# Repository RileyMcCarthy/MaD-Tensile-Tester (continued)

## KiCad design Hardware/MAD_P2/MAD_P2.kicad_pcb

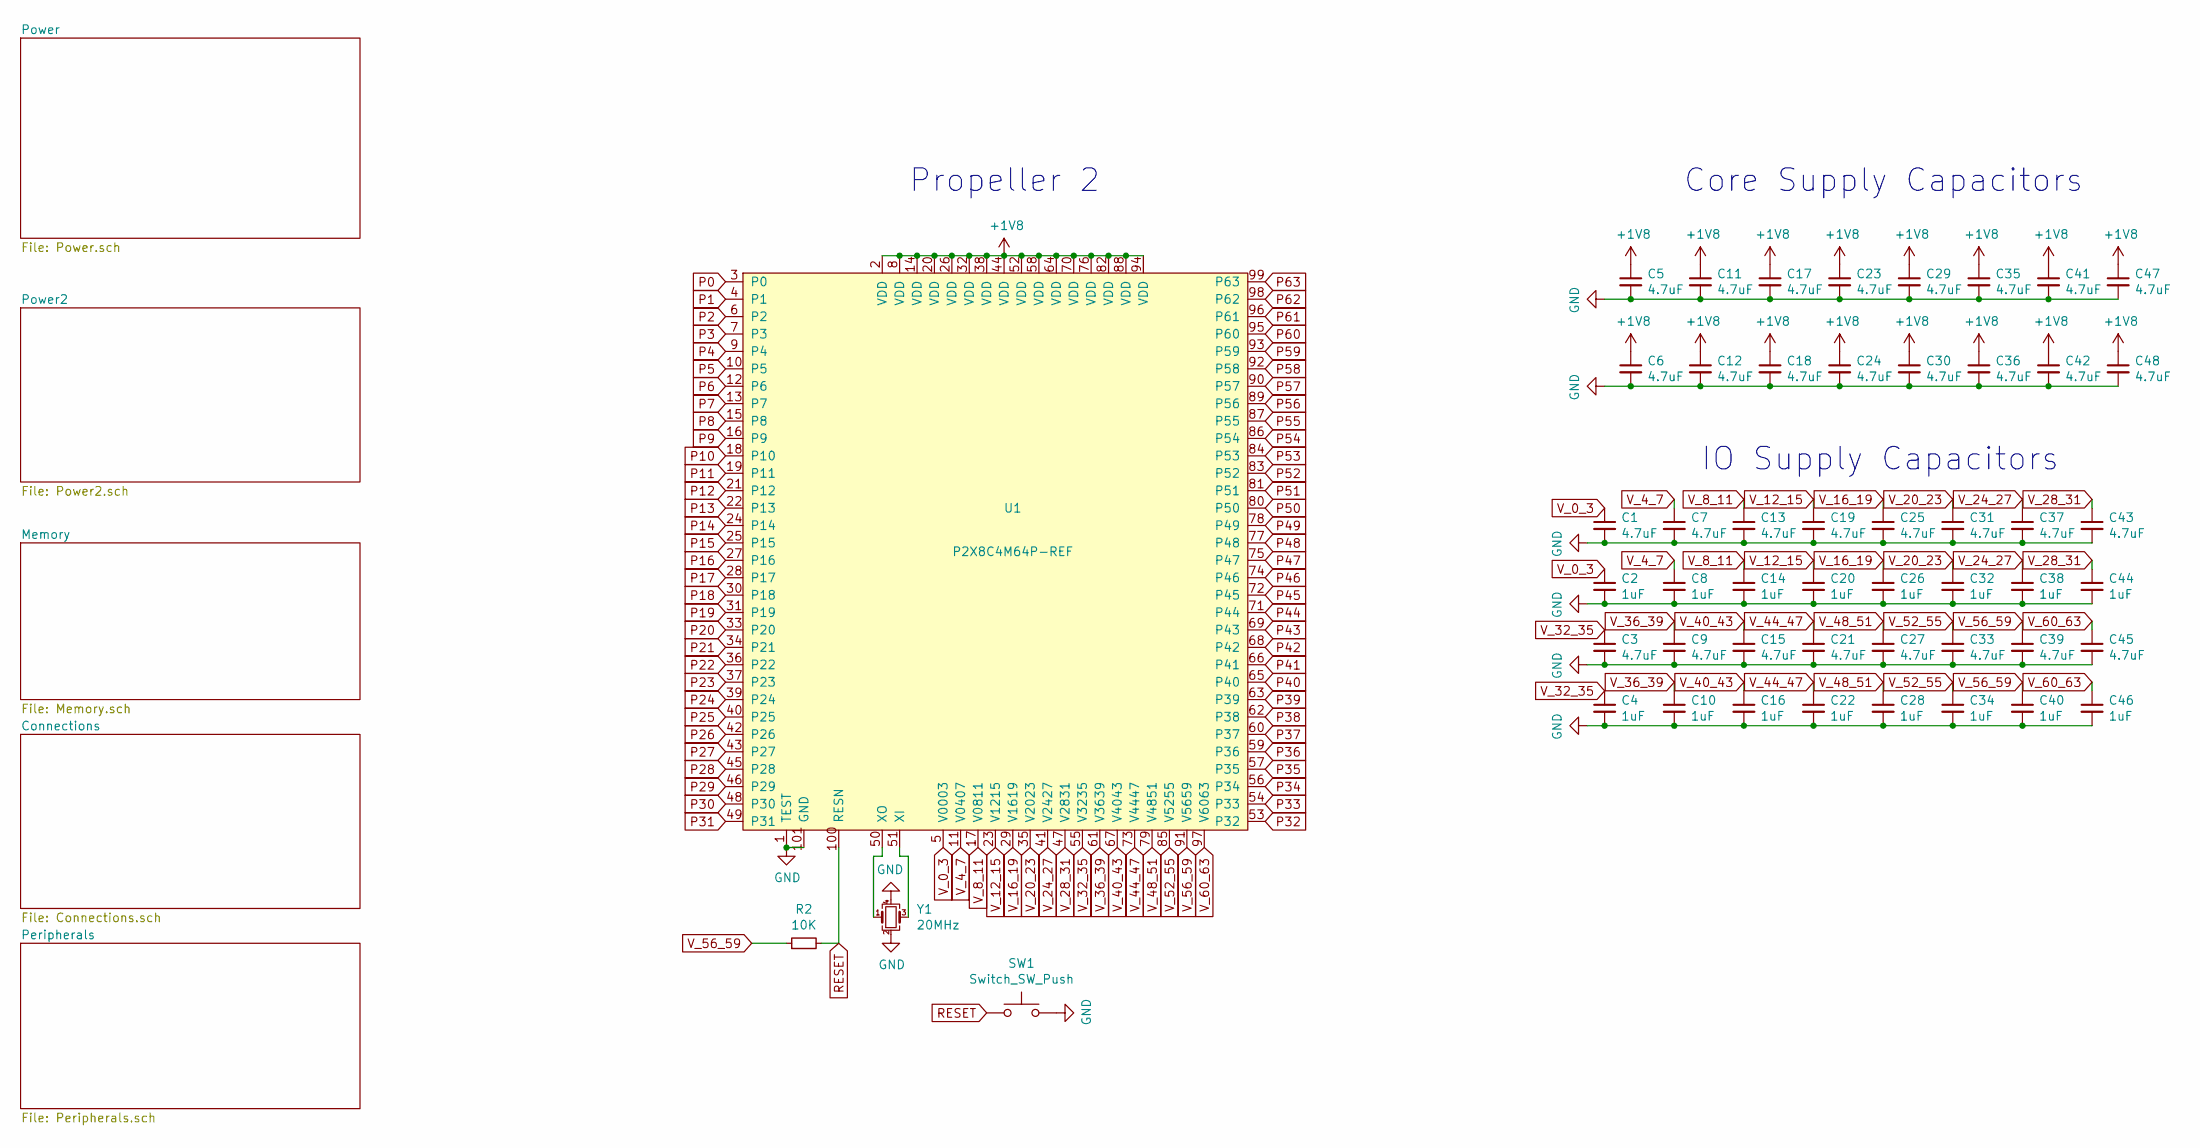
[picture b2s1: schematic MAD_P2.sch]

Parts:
C1, C3, C5, C6, C7, C9, C11, C12, C13, C15, C17, C18, C19, C21, C23, C24, C25, C27, C29, C30, C31, C33, C35, C36, C37, C39, C41, C42, C43, C45, C47, C48: 4.7uF; C_0603_1608Metric; LCSC C19666
C2, C4, C8, C10, C14, C16, C20, C22, C26, C28, C32, C34, C38, C40, C44, C46: 1uF; C_0603_1608Metric; LCSC C15849
R2: 10K; R_0603_1608Metric; LCSC C25804
SW1: Switch_SW_Push; SW_PUSH_6mm
U1: P2X8C4M64P-REF; TQFP-100-1EP_14x14mm_P0.5mm_EP5x5mm_ThermalVias; DIGIKEY 149-P2X8C4M64P-ND
Y1: 20MHz; Crystal_SMD_3225-4Pin_3.2x2.5mm; LCSC C110936

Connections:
+1V8: C5.1, C6.1, C11.1, C12.1, C17.1, C18.1, C23.1, C24.1, C29.1, C30.1, C35.1, C36.1, C41.1, C42.1, C47.1, C48.1, U1.2 (VDD), U1.8 (VDD), U1.14 (VDD), U1.20 (VDD), U1.26 (VDD), U1.32 (VDD), U1.38 (VDD), U1.44 (VDD), U1.52 (VDD), U1.58 (VDD), U1.64 (VDD), U1.70 (VDD), U1.76 (VDD), U1.82 (VDD), U1.88 (VDD), U1.94 (VDD); also elsewhere on the board
GND: C1.2, C2.2, C3.2, C4.2, C5.2, C6.2, C7.2, C8.2, C9.2, C10.2, C11.2, C12.2, C13.2, C14.2, C15.2, C16.2, C17.2, C18.2, C19.2, C20.2, C21.2, C22.2, C23.2, C24.2, C25.2, C26.2, C27.2, C28.2, C29.2, C30.2, C31.2, C32.2, C33.2, C34.2, C35.2, C36.2, C37.2, C38.2, C39.2, C40.2, C41.2, C42.2, C43.2, C44.2, C45.2, C46.2, C47.2, C48.2, SW1.2, U1.1 (TEST), U1.101 (GND), Y1.2, Y1.4; also elsewhere on the board
unnamed: U1.50 (XO), Y1.1
unnamed: U1.51 (XI), Y1.3
P0: U1.3 (P0); also elsewhere on the board
P1: U1.4 (P1); also elsewhere on the board
P2: U1.6 (P2); also elsewhere on the board
P3: U1.7 (P3); also elsewhere on the board
P4: U1.9 (P4); also elsewhere on the board
P5: U1.10 (P5); also elsewhere on the board
P6: U1.12 (P6); also elsewhere on the board
P7: U1.13 (P7); also elsewhere on the board
P8: U1.15 (P8); also elsewhere on the board
P9: U1.16 (P9); also elsewhere on the board
P10: U1.18 (P10); also elsewhere on the board
P11: U1.19 (P11); also elsewhere on the board
P12: U1.21 (P12); also elsewhere on the board
P13: U1.22 (P13); also elsewhere on the board
P14: U1.24 (P14); also elsewhere on the board
P15: U1.25 (P15); also elsewhere on the board
P16: U1.27 (P16); also elsewhere on the board
P17: U1.28 (P17); also elsewhere on the board
P18: U1.30 (P18); also elsewhere on the board
P19: U1.31 (P19); also elsewhere on the board
P20: U1.33 (P20); also elsewhere on the board
P21: U1.34 (P21); also elsewhere on the board
P22: U1.36 (P22); also elsewhere on the board
P23: U1.37 (P23); also elsewhere on the board
P24: U1.39 (P24); also elsewhere on the board
P25: U1.40 (P25); also elsewhere on the board
P26: U1.42 (P26); also elsewhere on the board
P27: U1.43 (P27); also elsewhere on the board
P28: U1.45 (P28); also elsewhere on the board
P29: U1.46 (P29); also elsewhere on the board
P30: U1.48 (P30); also elsewhere on the board
P31: U1.49 (P31); also elsewhere on the board
P32: U1.53 (P32); also elsewhere on the board
P33: U1.54 (P33); also elsewhere on the board
P34: U1.56 (P34); also elsewhere on the board
P35: U1.57 (P35); also elsewhere on the board
P36: U1.59 (P36); also elsewhere on the board
P37: U1.60 (P37); also elsewhere on the board
P38: U1.62 (P38); also elsewhere on the board
P39: U1.63 (P39); also elsewhere on the board
P40: U1.65 (P40); also elsewhere on the board
P41: U1.66 (P41); also elsewhere on the board
P42: U1.68 (P42); also elsewhere on the board
P43: U1.69 (P43); also elsewhere on the board
P44: U1.71 (P44); also elsewhere on the board
P45: U1.72 (P45); also elsewhere on the board
P46: U1.74 (P46); also elsewhere on the board
P47: U1.75 (P47); also elsewhere on the board
P48: U1.77 (P48); also elsewhere on the board
P49: U1.78 (P49); also elsewhere on the board
P50: U1.80 (P50); also elsewhere on the board
P51: U1.81 (P51); also elsewhere on the board
P52: U1.83 (P52); also elsewhere on the board
P53: U1.84 (P53); also elsewhere on the board
P54: U1.86 (P54); also elsewhere on the board
P55: U1.87 (P55); also elsewhere on the board
P56: U1.89 (P56); also elsewhere on the board
P57: U1.90 (P57); also elsewhere on the board
P58: U1.92 (P58); also elsewhere on the board
P59: U1.93 (P59); also elsewhere on the board
P60: U1.95 (P60); also elsewhere on the board
P61: U1.96 (P61); also elsewhere on the board
P62: U1.98 (P62); also elsewhere on the board
P63: U1.99 (P63); also elsewhere on the board
RESET: R2.2, SW1.1, U1.100 (RESN); also elsewhere on the board
V_0_3: C1.1, C2.1, C7.1, C8.1, C13.1, C14.1, C19.1, C20.1, C25.1, C26.1, C31.1, C32.1, C37.1, C38.1, C43.1, C44.1, U1.5 (V0003), U1.11 (V0407), U1.17 (V0811), U1.23 (V1215), U1.29 (V1619), U1.35 (V2023), U1.41 (V2427), U1.47 (V2831); also elsewhere on the board
V_32_35: C3.1, C4.1, C9.1, C10.1, C15.1, C16.1, C21.1, C22.1, C27.1, C28.1, C33.1, C34.1, C39.1, C40.1, C45.1, C46.1, R2.1, U1.55 (V3235), U1.61 (V3639), U1.67 (V4043), U1.73 (V4447), U1.79 (V4851), U1.85 (V5255), U1.91 (V5659), U1.97 (V6063); also elsewhere on the board

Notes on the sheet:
Core Supply Capacitors
IO Supply Capacitors
Propeller 2

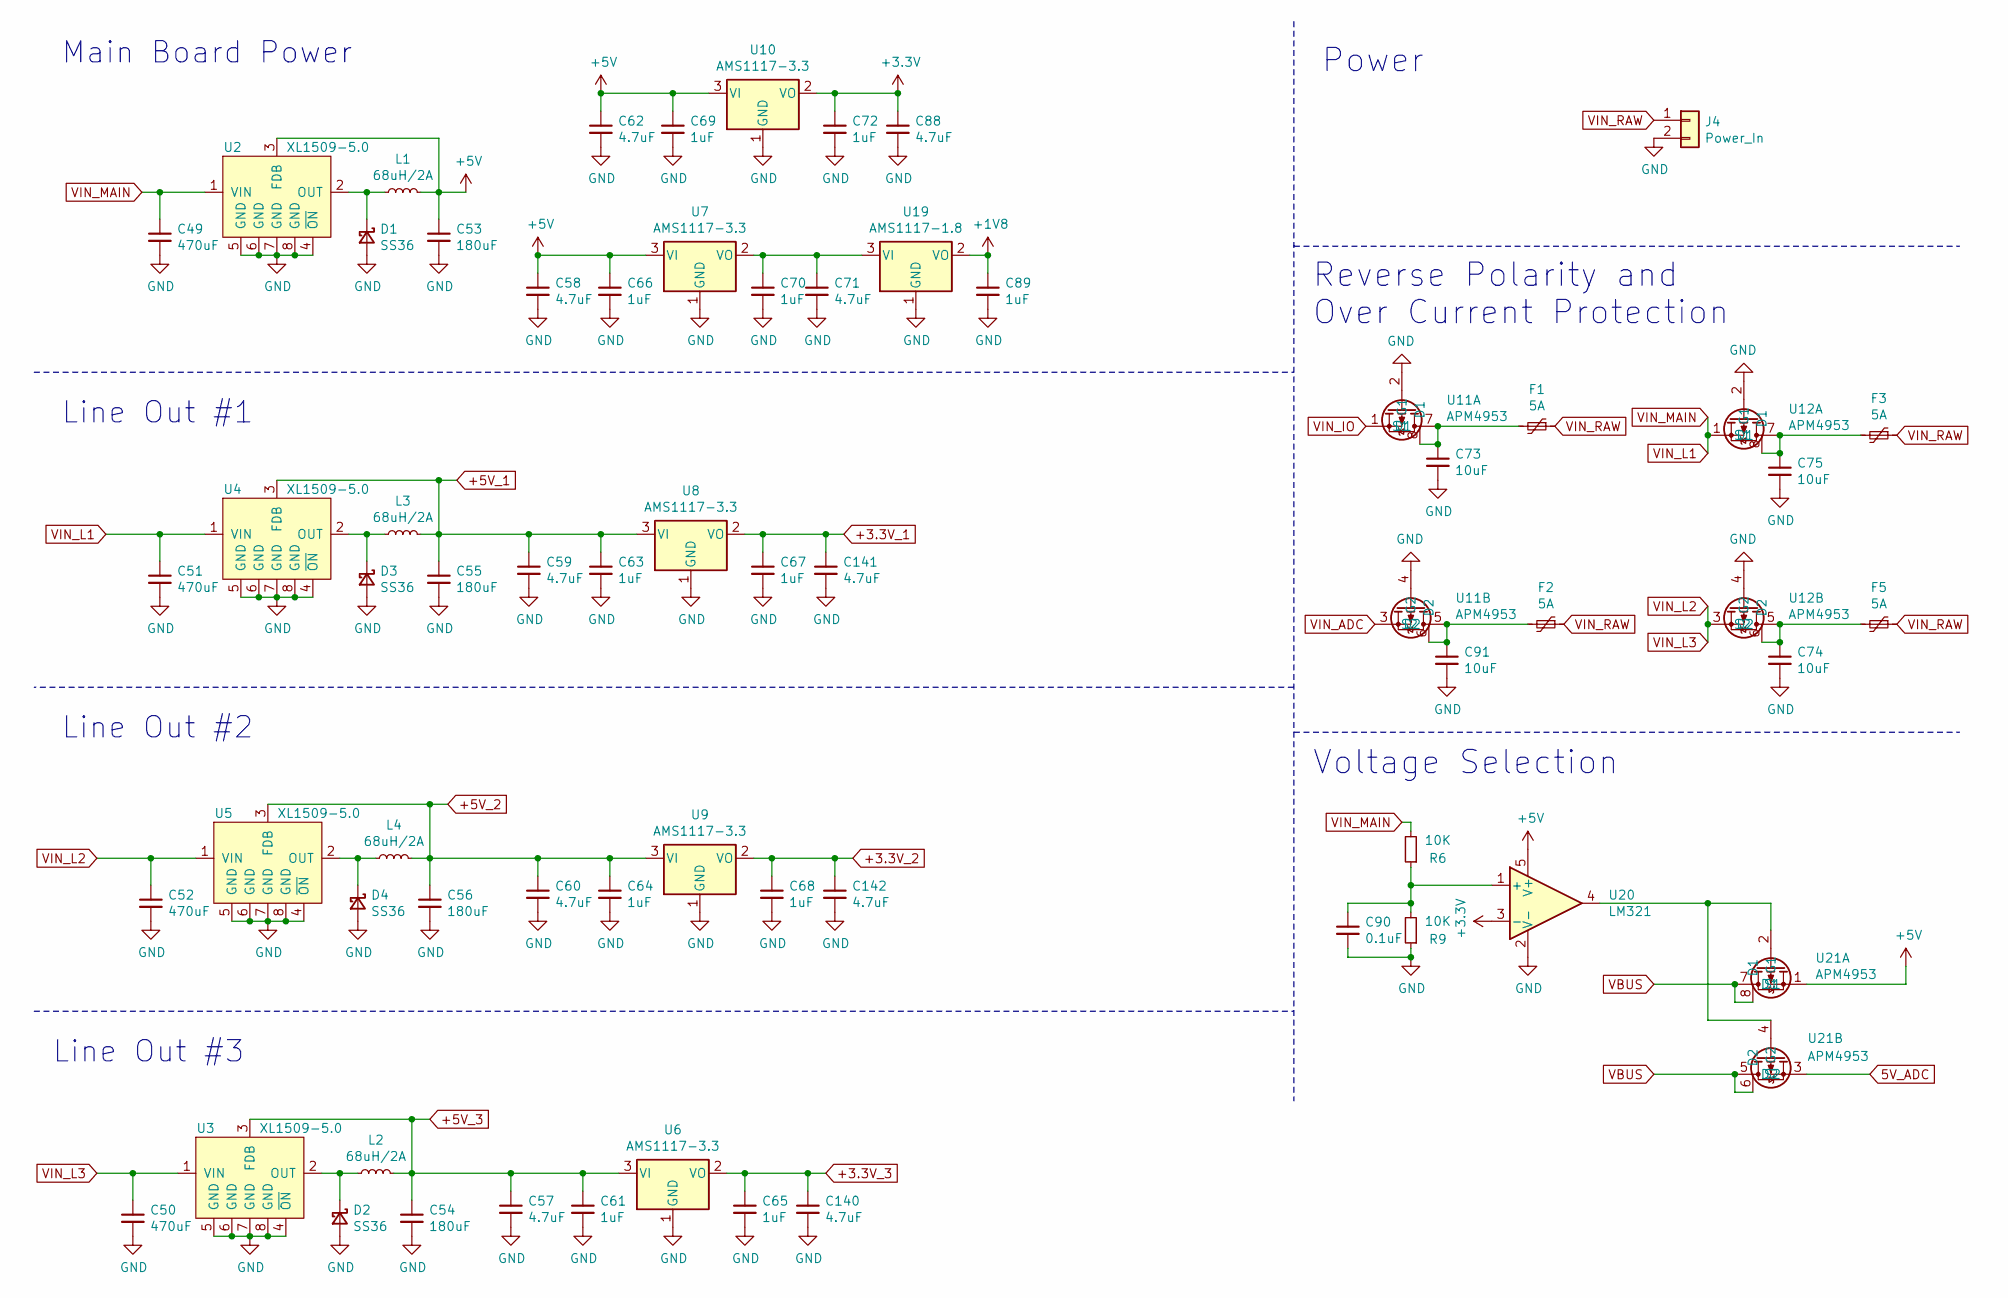
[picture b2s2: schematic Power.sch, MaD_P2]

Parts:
C49, C50, C51, C52: 470uF; C_Elec_10x10.2; LCSC C3350
C53, C54, C55, C56: 180uF; C_Elec_6.3x7.7; LCSC C413657
C57, C58, C59, C60, C62, C71, C88, C140, C141, C142: 4.7uF; C_0603_1608Metric; LCSC C19666
C61, C63, C64, C65, C66, C67, C68, C69, C70, C72, C89: 1uF; C_0603_1608Metric; LCSC C15849
C73, C74, C75, C91: 10uF; C_0805_2012Metric; LCSC C15850
C90: 0.1uF; C_0603_1608Metric; LCSC C14663
D1, D2, D3, D4: SS36; D_SMC; LCSC C35722
F1, F2, F3, F5: 5A; C_Rect_L4.0mm_W2.5mm_P2.50mm; DIGIKEY PTR030V0500-BK-ND
J4: Power_In; 0705530001; DIGIKEY WM4900-ND
L1, L2, L3, L4: 68uH/2A; L_10.4x10.4_H4.8; LCSC C497902
R6, R9: 10K; R_0603_1608Metric; LCSC C25804
U2, U3, U4, U5: XL1509-5.0; SOP-8_3.9x4.9mm_P1.27mm; LCSC C61063
U6, U7, U8, U9, U10: AMS1117-3.3; SOT-223-3_TabPin2; LCSC C6186
U11, U12, U21: APM4953; SOP-8_3.9x4.9mm_P1.27mm; LCSC C20897
U19: AMS1117-1.8; SOT-223-3_TabPin2; LCSC C6185
U20: LM321; SOT-23-5; LCSC C131103

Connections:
5V_ADC: U21.3 (S2); also elsewhere on the board
+1V8: C89.1, U19.2 (VO); also elsewhere on the board
+3.3V_1: C67.1, C141.1, U8.2 (VO); also elsewhere on the board
+3.3V_2: C68.1, C142.1, U9.2 (VO); also elsewhere on the board
+3.3V_3: C65.1, C140.1, U6.2 (VO); also elsewhere on the board
+3V3: C72.1, C88.1, U10.2 (VO), U20.3 (-); also elsewhere on the board
+5V: C53.1, C58.1, C62.1, C66.1, C69.1, L1.2, U2.3 (FDB), U7.3 (VI), U10.3 (VI), U20.5 (V+), U21.1 (S1); also elsewhere on the board
+5V_1: C55.1, C59.1, C63.1, L3.2, U4.3 (FDB), U8.3 (VI); also elsewhere on the board
+5V_2: C56.1, C60.1, C64.1, L4.2, U5.3 (FDB), U9.3 (VI); also elsewhere on the board
+5V_3: C54.1, C57.1, C61.1, L2.2, U3.3 (FDB), U6.3 (VI); also elsewhere on the board
GND: C49.2, C50.2, C51.2, C52.2, C53.2, C54.2, C55.2, C56.2, C57.2, C58.2, C59.2, C60.2, C61.2, C62.2, C63.2, C64.2, C65.2, C66.2, C67.2, C68.2, C69.2, C70.2, C71.2, C72.2, C73.2, C74.2, C75.2, C88.2, C89.2, C90.2, C91.2, C140.2, C141.2, C142.2, D1.2 (A), D2.2 (A), D3.2 (A), D4.2 (A), J4.2, R9.1, U2.4 (~ON), U2.5 (GND), U2.6 (GND), U2.7 (GND), U2.8 (GND), U3.4 (~ON), U3.5 (GND), U3.6 (GND), U3.7 (GND), U3.8 (GND), U4.4 (~ON), U4.5 (GND), U4.6 (GND), U4.7 (GND), U4.8 (GND), U5.4 (~ON), U5.5 (GND), U5.6 (GND), U5.7 (GND), U5.8 (GND), U6.1 (GND), U7.1 (GND), U8.1 (GND), U9.1 (GND), U10.1 (GND), U11.2 (G1), U11.4 (G2), U12.2 (G1), U12.4 (G2), U19.1 (GND), U20.2 (V-); also elsewhere on the board
unnamed: C70.1, C71.1, U7.2 (VO), U19.3 (VI)
unnamed: C73.1, F1.2, U11.7 (D1), U11.8 (D1)
unnamed: C74.1, F5.2, U12.5 (D2), U12.6 (D2)
unnamed: C75.1, F3.2, U12.7 (D1), U12.8 (D1)
unnamed: C90.1, R6.1, R9.2, U20.1 (+)
unnamed: C91.1, F2.2, U11.5 (D2), U11.6 (D2)
unnamed: D1.1 (K), L1.1, U2.2 (OUT)
unnamed: D2.1 (K), L2.1, U3.2 (OUT)
unnamed: D3.1 (K), L3.1, U4.2 (OUT)
unnamed: D4.1 (K), L4.1, U5.2 (OUT)
unnamed: U20.4, U21.2 (G1), U21.4 (G2)
VBUS: U21.5 (D2), U21.6 (D2), U21.7 (D1), U21.8 (D1); also elsewhere on the board
VIN_ADC: U11.3 (S2); also elsewhere on the board
VIN_IO: U11.1 (S1); also elsewhere on the board
VIN_L1: C49.1, C51.1, R6.2, U2.1 (VIN), U4.1 (VIN), U12.1 (S1); also elsewhere on the board
VIN_L2: C50.1, C52.1, U3.1 (VIN), U5.1 (VIN), U12.3 (S2); also elsewhere on the board
VIN_RAW: F1.1, F2.1, F3.1, F5.1, J4.1

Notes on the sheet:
Main Board Power
Line Out #1
Line Out #2
Line Out #3
Reverse Polarity and Over Current Protection
Power
Voltage Selection

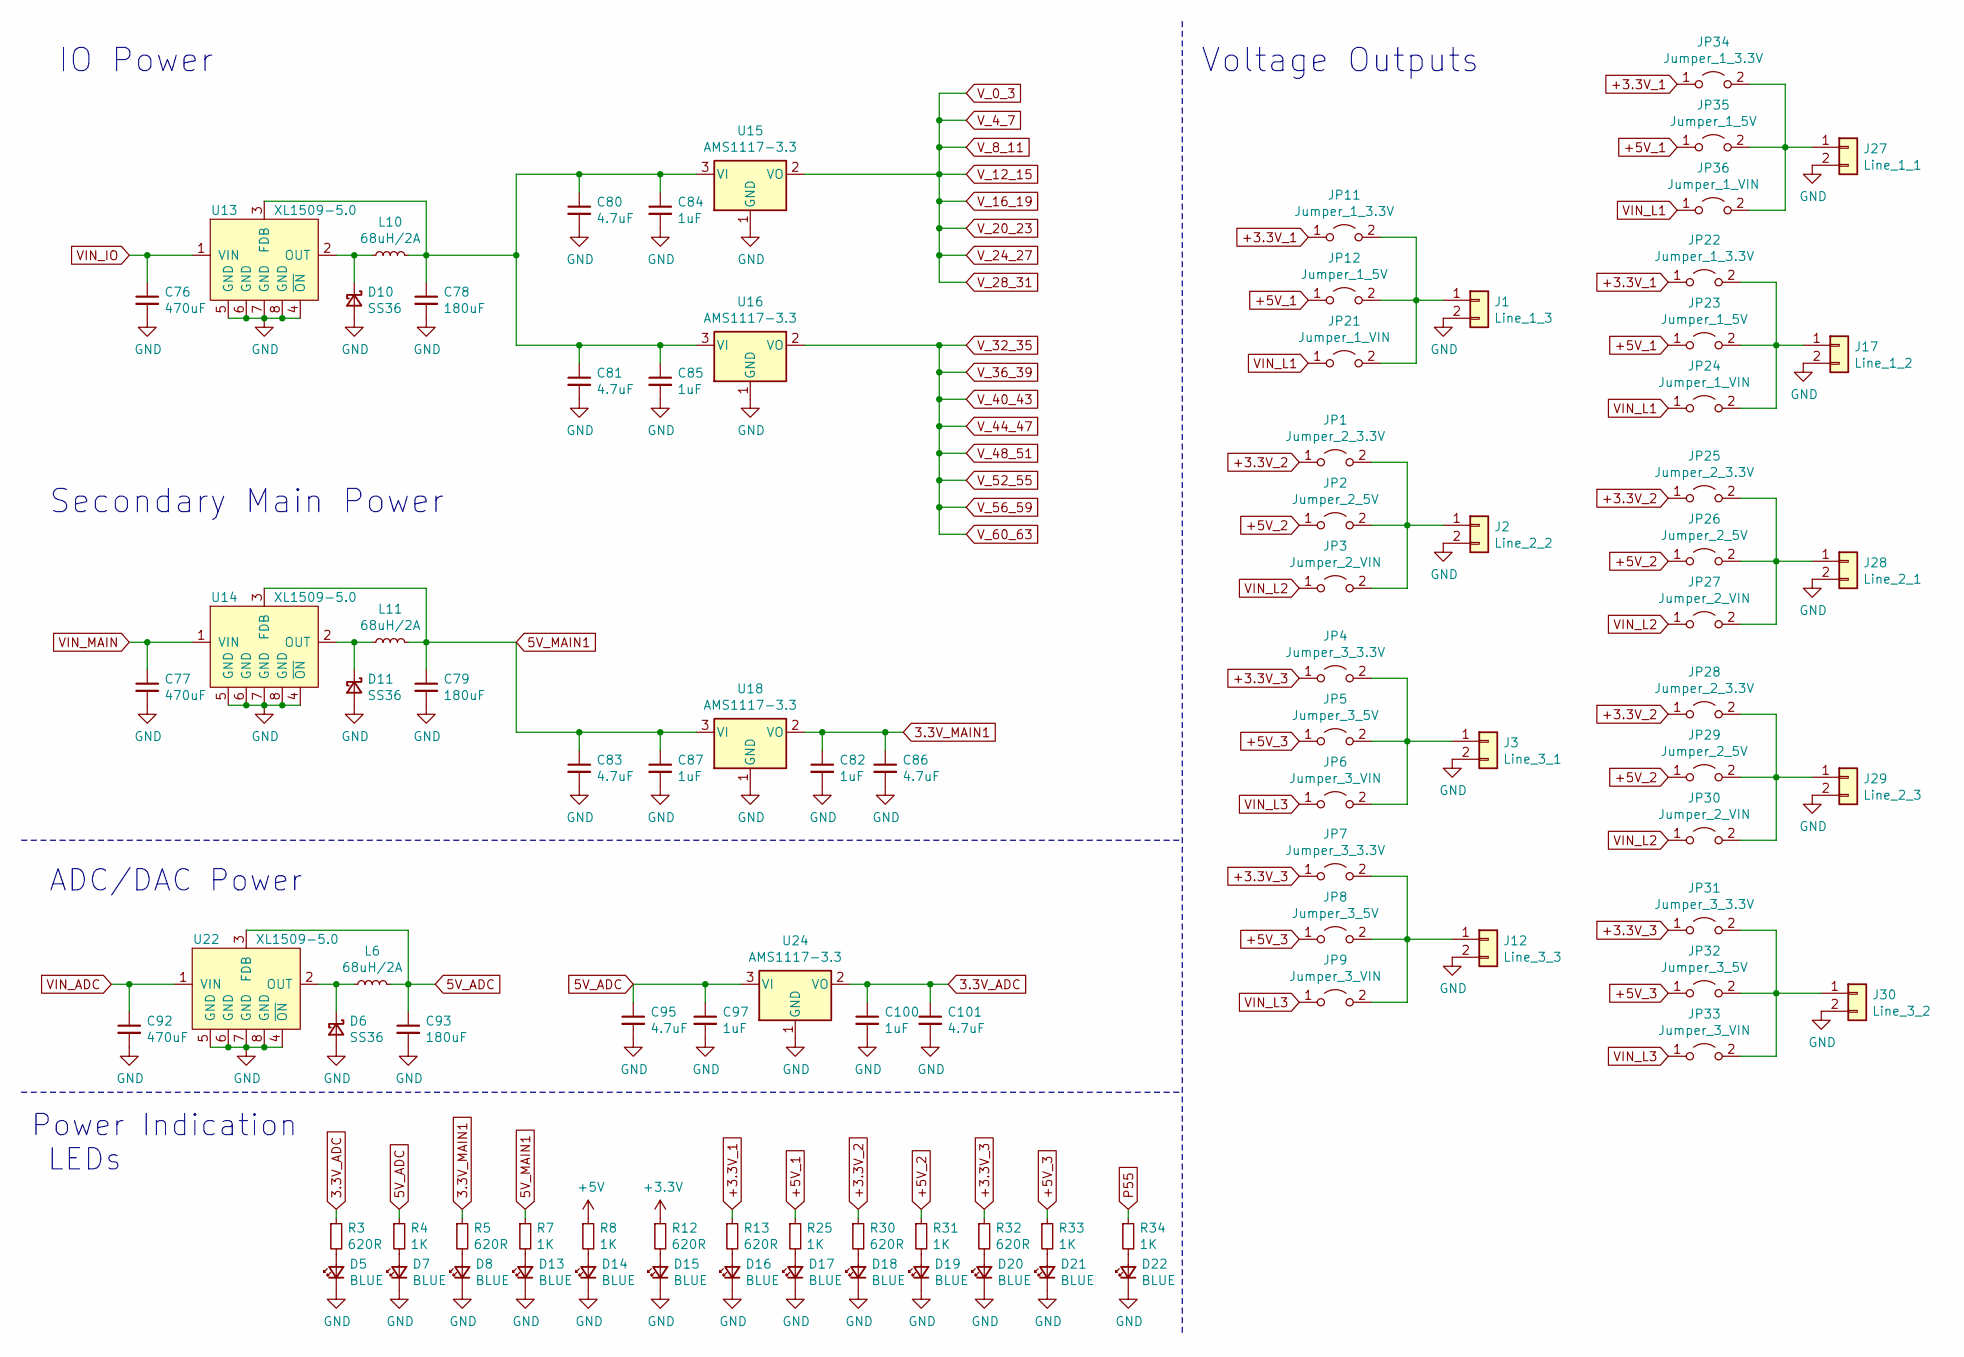
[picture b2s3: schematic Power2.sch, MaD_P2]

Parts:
C76, C77, C92: 470uF; C_Elec_10x10.2; LCSC C3350
C78, C79, C93: 180uF; C_Elec_6.3x7.7; LCSC C413657
C80, C81, C83, C86, C95, C101: 4.7uF; C_0603_1608Metric; LCSC C19666
C82, C84, C85, C87, C97, C100: 1uF; C_0603_1608Metric; LCSC C15849
D5, D7, D8, D13, D14, D15, D16, D17, D18, D19, D20, D21, D22: BLUE; LED_0603_1608Metric; LCSC C72041
D6, D10, D11: SS36; D_SMC; LCSC C35722
J1: Line_1_3; 0705530001; DIGIKEY WM4900-ND
J2: Line_2_2; 0705530001; DIGIKEY WM4900-ND
J3: Line_3_1; 0705530001; DIGIKEY WM4900-ND
J12: Line_3_3; 0705530001; DIGIKEY WM4900-ND
J17: Line_1_2; 0705530001; DIGIKEY WM4900-ND
J27: Line_1_1; 0705530001; DIGIKEY WM4900-ND
J28: Line_2_1; 0705530001; DIGIKEY WM4900-ND
J29: Line_2_3; 0705530001; DIGIKEY WM4900-ND
J30: Line_3_2; 0705530001; DIGIKEY WM4900-ND
JP1, JP25, JP28: Jumper_2_3.3V; SolderJumper-2_P1.3mm_Open_Pad1.0x1.5mm
JP2, JP26, JP29: Jumper_2_5V; SolderJumper-2_P1.3mm_Open_Pad1.0x1.5mm
JP3, JP27, JP30: Jumper_2_VIN; SolderJumper-2_P1.3mm_Open_Pad1.0x1.5mm
JP4, JP7, JP31: Jumper_3_3.3V; SolderJumper-2_P1.3mm_Open_Pad1.0x1.5mm
JP5, JP8, JP32: Jumper_3_5V; SolderJumper-2_P1.3mm_Open_Pad1.0x1.5mm
JP6, JP9, JP33: Jumper_3_VIN; SolderJumper-2_P1.3mm_Open_Pad1.0x1.5mm
JP11, JP22, JP34: Jumper_1_3.3V; SolderJumper-2_P1.3mm_Open_Pad1.0x1.5mm
JP12, JP23, JP35: Jumper_1_5V; SolderJumper-2_P1.3mm_Open_Pad1.0x1.5mm
JP21, JP24, JP36: Jumper_1_VIN; SolderJumper-2_P1.3mm_Open_Pad1.0x1.5mm
L6, L10, L11: 68uH/2A; L_10.4x10.4_H4.8; LCSC C497902
R3, R5, R12, R13, R30, R32: 620R; R_0603_1608Metric; LCSC C23220
R4, R7, R8, R25, R31, R33, R34: 1K; R_0603_1608Metric; LCSC C21190
U13, U14, U22: XL1509-5.0; SOP-8_3.9x4.9mm_P1.27mm; LCSC C61063
U15, U16, U18, U24: AMS1117-3.3; SOT-223-3_TabPin2; LCSC C6186

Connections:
3.3V_ADC: C100.1, C101.1, R3.1, U24.2 (VO); also elsewhere on the board
3.3V_MAIN1: C82.1, C86.1, R5.1, U18.2 (VO); also elsewhere on the board
5V_ADC: C93.1, C95.1, C97.1, L6.2, R4.1, U22.3 (FDB), U24.3 (VI); also elsewhere on the board
5V_MAIN1: C79.1, C83.1, C87.1, L11.2, R7.1, U14.3 (FDB), U18.3 (VI); also elsewhere on the board
+3.3V_1: JP11.1 (A), JP22.1 (A), JP34.1 (A), R13.1; also elsewhere on the board
+3.3V_2: JP1.1 (A), JP25.1 (A), JP28.1 (A), R30.1; also elsewhere on the board
+3.3V_3: JP4.1 (A), JP7.1 (A), JP31.1 (A), R32.1; also elsewhere on the board
+3V3: R12.1; also elsewhere on the board
+5V: R8.1; also elsewhere on the board
+5V_1: JP12.1 (A), JP23.1 (A), JP35.1 (A), R25.1; also elsewhere on the board
+5V_2: JP2.1 (A), JP26.1 (A), JP29.1 (A), R31.1; also elsewhere on the board
+5V_3: JP5.1 (A), JP8.1 (A), JP32.1 (A), R33.1; also elsewhere on the board
GND: C76.2, C77.2, C78.2, C79.2, C80.2, C81.2, C82.2, C83.2, C84.2, C85.2, C86.2, C87.2, C92.2, C93.2, C95.2, C97.2, C100.2, C101.2, D5.1 (K), D6.2 (A), D7.1 (K), D8.1 (K), D10.2 (A), D11.2 (A), D13.1 (K), D14.1 (K), D15.1 (K), D16.1 (K), D17.1 (K), D18.1 (K), D19.1 (K), D20.1 (K), D21.1 (K), D22.1 (K), J1.2, J2.2, J3.2, J12.2, J17.2, J27.2, J28.2, J29.2, J30.2, U13.4 (~ON), U13.5 (GND), U13.6 (GND), U13.7 (GND), U13.8 (GND), U14.4 (~ON), U14.5 (GND), U14.6 (GND), U14.7 (GND), U14.8 (GND), U15.1 (GND), U16.1 (GND), U18.1 (GND), U22.4 (~ON), U22.5 (GND), U22.6 (GND), U22.7 (GND), U22.8 (GND), U24.1 (GND); also elsewhere on the board
unnamed: C78.1, C80.1, C81.1, C84.1, C85.1, L10.2, U13.3 (FDB), U15.3 (VI), U16.3 (VI)
unnamed: D5.2 (A), R3.2
unnamed: D6.1 (K), L6.1, U22.2 (OUT)
unnamed: D7.2 (A), R4.2
unnamed: D8.2 (A), R5.2
unnamed: D10.1 (K), L10.1, U13.2 (OUT)
unnamed: D11.1 (K), L11.1, U14.2 (OUT)
unnamed: D13.2 (A), R7.2
unnamed: D14.2 (A), R8.2
unnamed: D15.2 (A), R12.2
unnamed: D16.2 (A), R13.2
unnamed: D17.2 (A), R25.2
unnamed: D18.2 (A), R30.2
unnamed: D19.2 (A), R31.2
unnamed: D20.2 (A), R32.2
unnamed: D21.2 (A), R33.2
unnamed: D22.2 (A), R34.2
unnamed: J1.1, JP11.2 (B), JP12.2 (B), JP21.2 (B)
unnamed: J2.1, JP1.2 (B), JP2.2 (B), JP3.2 (B)
unnamed: J3.1, JP4.2 (B), JP5.2 (B), JP6.2 (B)
unnamed: J12.1, JP7.2 (B), JP8.2 (B), JP9.2 (B)
unnamed: J17.1, JP22.2 (B), JP23.2 (B), JP24.2 (B)
unnamed: J27.1, JP34.2 (B), JP35.2 (B), JP36.2 (B)
unnamed: J28.1, JP25.2 (B), JP26.2 (B), JP27.2 (B)
unnamed: J29.1, JP28.2 (B), JP29.2 (B), JP30.2 (B)
unnamed: J30.1, JP31.2 (B), JP32.2 (B), JP33.2 (B)
P55: R34.1; also elsewhere on the board
VIN_ADC: C92.1, U22.1 (VIN); also elsewhere on the board
VIN_IO: C76.1, U13.1 (VIN); also elsewhere on the board
VIN_L1: C77.1, JP21.1 (A), JP24.1 (A), JP36.1 (A), U14.1 (VIN); also elsewhere on the board
VIN_L2: JP3.1 (A), JP6.1 (A), JP9.1 (A), JP27.1 (A), JP30.1 (A), JP33.1 (A); also elsewhere on the board
V_0_3: U15.2 (VO); also elsewhere on the board
V_32_35: U16.2 (VO); also elsewhere on the board

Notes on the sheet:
ADC/DAC Power
IO Power
Secondary Main Power
Voltage Outputs
Power Indication LEDs

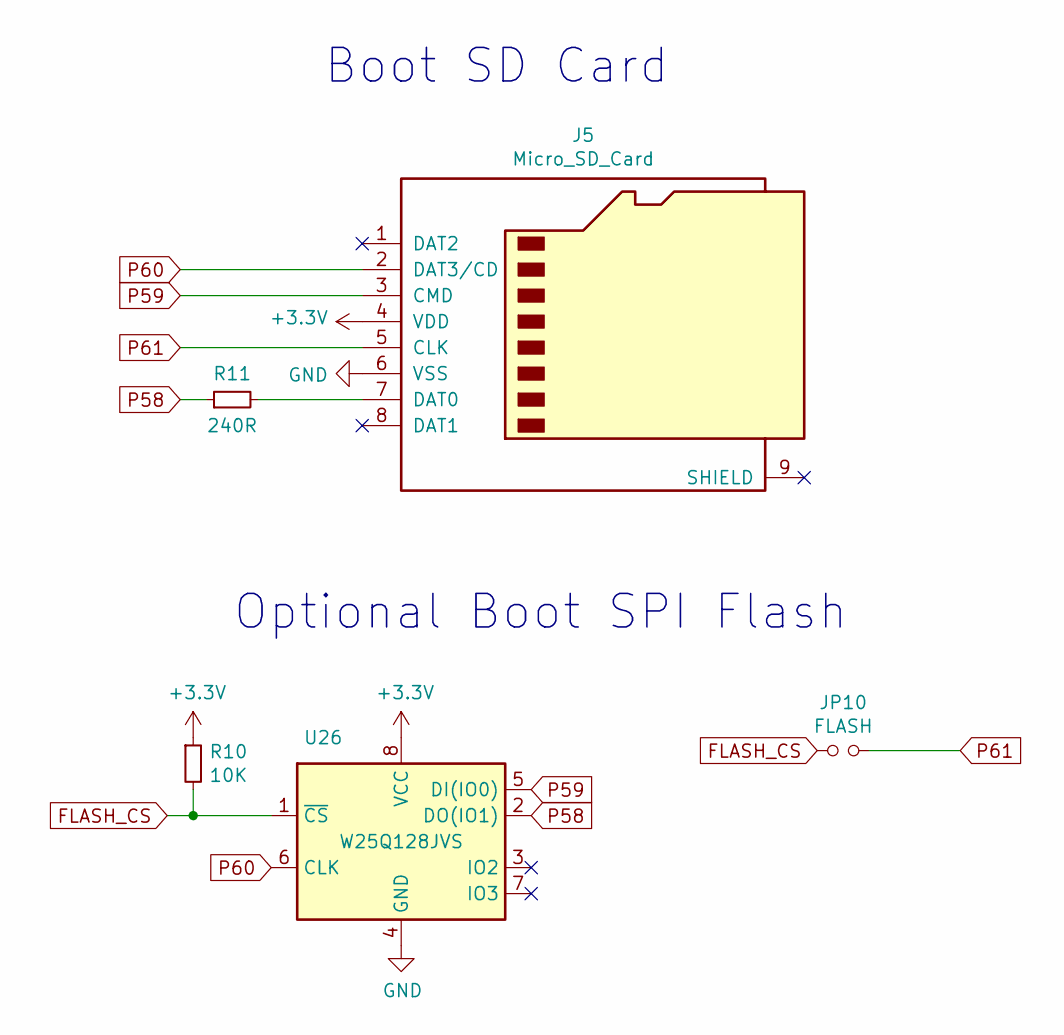
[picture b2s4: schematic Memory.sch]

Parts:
J5: Micro_SD_Card; microSD_HC_Hirose_DM3D-SF; DIGIKEY 732-3820-2-ND
JP10: FLASH; PinHeader_1x02_P2.54mm_Vertical
R10: 10K; R_0603_1608Metric; LCSC C25804
R11: 240R; R_0603_1608Metric; LCSC C23350
U26: W25Q128JVS; SOIC-8_5.23x5.23mm_P1.27mm; LCSC C97521

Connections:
+3V3: J5.4 (VDD), R10.1, U26.8 (VCC); also elsewhere on the board
FLASH_CS: JP10.1, R10.2, U26.1 (~CS)
GND: J5.6 (VSS), U26.4 (GND); also elsewhere on the board
unnamed: J5.7 (DAT0), R11.2
P58: R11.1, U26.2 (DO(IO1)); also elsewhere on the board
P59: J5.3 (CMD), U26.5 (DI(IO0)); also elsewhere on the board
P60: J5.2 (DAT3/CD), U26.6 (CLK); also elsewhere on the board
P61: J5.5 (CLK), JP10.2; also elsewhere on the board

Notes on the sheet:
Optional Boot SPI Flash
Boot SD Card
